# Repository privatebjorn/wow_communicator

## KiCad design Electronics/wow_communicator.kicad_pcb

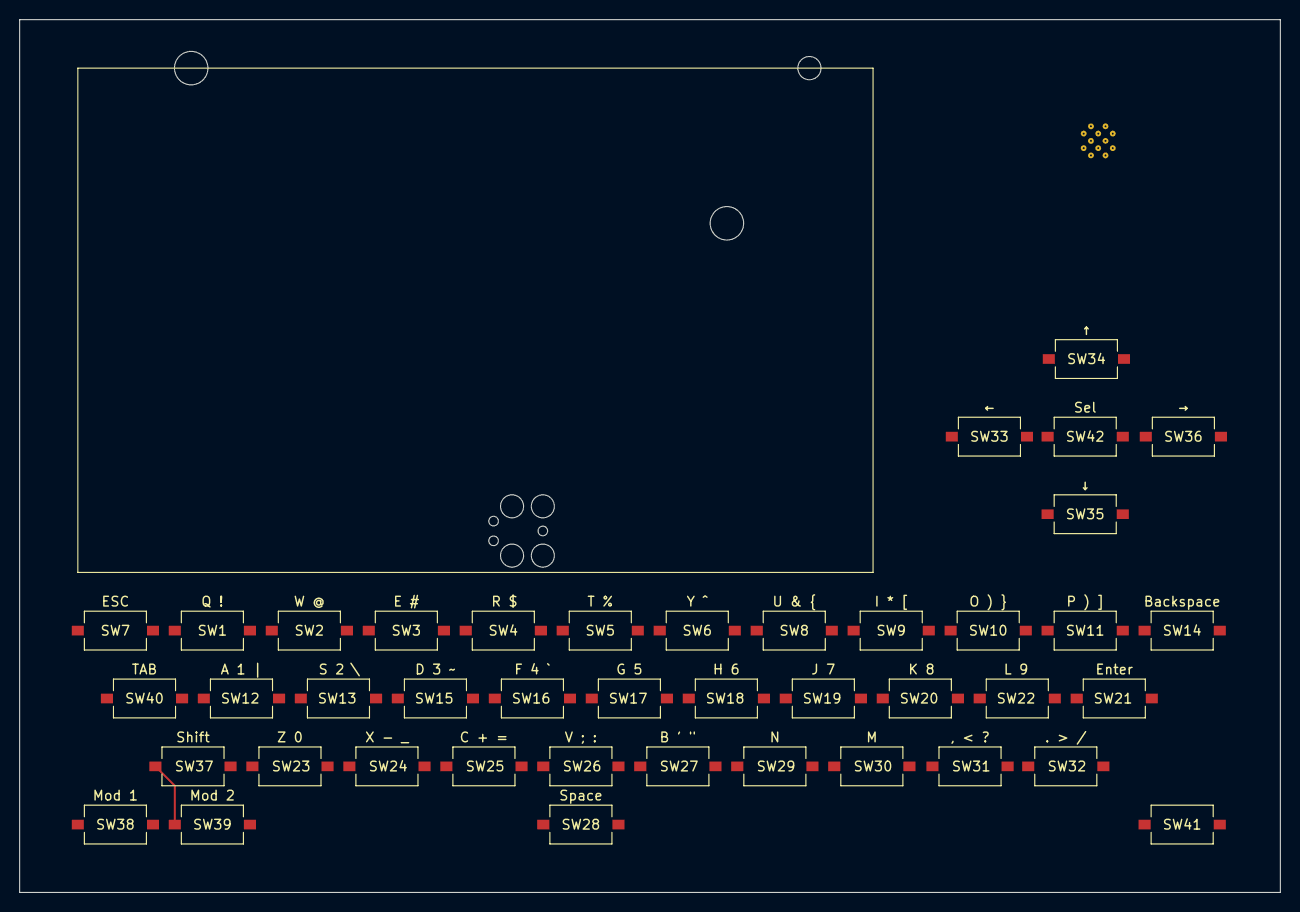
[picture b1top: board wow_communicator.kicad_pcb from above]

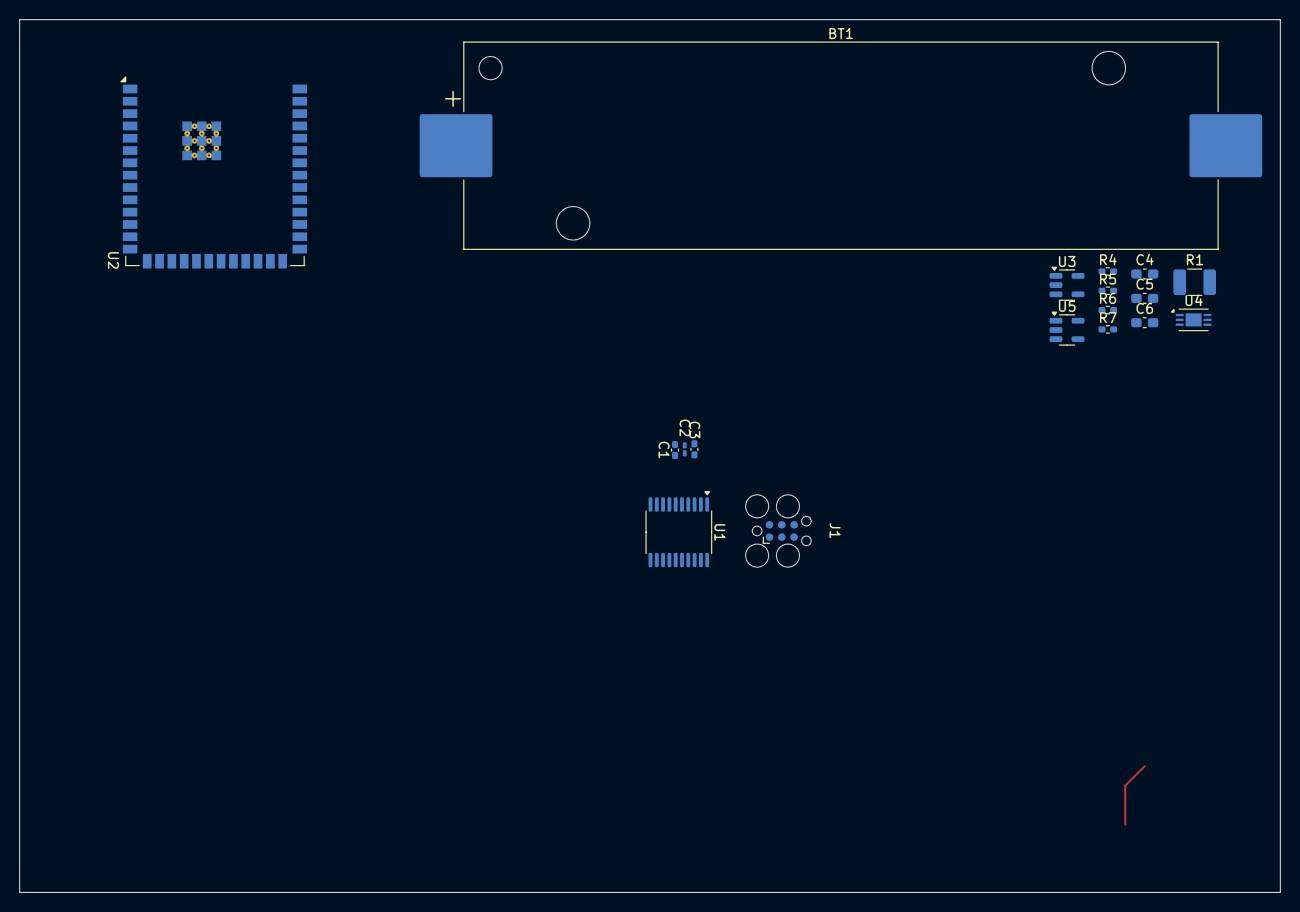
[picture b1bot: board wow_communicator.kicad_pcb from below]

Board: 4 copper layers, 130.0 x 90.0 mm, 60 parts (18 on the bottom side), 24 nets.

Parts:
BT1: 18650; BatteryHolder_Keystone_1042_1x18650
C1, C3: 100n; C_0402_1005Metric_Pad0.74x0.62mm_HandSolder
C2: 4.7u; C_0201_0603Metric_Pad0.64x0.40mm_HandSolder
C4: 1u; C_0603_1608Metric_Pad1.08x0.95mm_HandSolder
C5, C6: 10u; C_0603_1608Metric_Pad1.08x0.95mm_HandSolder
J1: DEBUG; Tag-Connect_TC2030-IDC-FP_2x03_P1.27mm_Vertical
R1: 100m; R_1210_3225Metric_Pad1.30x2.65mm_HandSolder
R4: 2k; R_0402_1005Metric_Pad0.72x0.64mm_HandSolder
R5, R6: 5.1k; R_0402_1005Metric_Pad0.72x0.64mm_HandSolder
R7: 1M; R_0402_1005Metric_Pad0.72x0.64mm_HandSolder
SW1, SW2, SW3, SW4, SW5, SW6, SW7, SW8, SW9, SW10, SW11, SW12, SW13, SW14, SW15, SW16, SW17, SW18, SW19, SW20, SW21, SW22, SW23, SW24, SW25, SW26, SW27, SW28, SW29, SW30, SW31, SW32, SW33, SW34, SW35, SW36, SW37, SW38, SW39, SW40, SW41, SW42: SW_SPST; SW_Tactile_SPST_NO_Straight_CK_PTS636Sx25SMTRLFS
U1: STM32C011F6Px; TSSOP-20_4.4x6.5mm_P0.65mm
U2: ESP32-S3-WROOM-2
U3: TLV75733PDBV; SOT-23-5
U4: LTC2942; DFN-6-1EP_3x2mm_P0.5mm_EP1.65x1.35mm
U5: MCP73812T-435I-OT; SOT-23-5

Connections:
0: BT1.2 (-), C1.2, C2.2, C3.2, C4.2, C5.2, C6.2, J1.5 (GND), R4.2, R5.2, R6.2, R7.2, U1.5 (VSS), U3.2 (GND), U4.2 (GND), U5.2 (V_{SS})
+3V3: C2.1, C3.1, C5.1, C6.1, J1.1 (VCC), U1.4 (VDD), U3.5 (OUT)
/keyboard_matrix/DEBUG_SWCLK: J1.4 (SWCLK), U1.19 (DEBUG_SWCLK)
/keyboard_matrix/DEBUG_SWDIO: J1.2 (SWDIO), U1.18 (DEBUG_SWDIO)
/keyboard_matrix/NRESET: C1.1, J1.3 (~RESET), U1.6 (PF2)
unnamed: BT1.1 (+), R1.2, U4.6 (SENSE-)
unnamed: SW1.1 (A), SW2.1 (A), SW3.1 (A), SW4.1 (A), SW5.1 (A), SW6.1 (A), SW7.1 (A), U1.15 (PA8)
unnamed: SW1.2 (B), SW8.2 (B), SW15.2 (B), SW22.2 (B), SW29.2 (B), SW36.2 (B), U1.14 (PA7)
unnamed: SW8.1 (A), SW9.1 (A), SW10.1 (A), SW11.1 (A), SW12.1 (A), SW13.1 (A), SW14.1 (A), U1.20 (PB6)
unnamed: SW3.2 (B), SW10.2 (B), SW17.2 (B), SW24.2 (B), SW31.2 (B), SW38.2 (B), U1.12 (PA5)
unnamed: SW4.2 (B), SW11.2 (B), SW18.2 (B), SW25.2 (B), SW32.2 (B), SW39.2 (B), U1.11 (PA4)
unnamed: SW5.2 (B), SW12.2 (B), SW19.2 (B), SW26.2 (B), SW33.2 (B), SW40.2 (B), U1.1 (PB7)
unnamed: SW6.2 (B), SW13.2 (B), SW20.2 (B), SW27.2 (B), SW34.2 (B), SW41.2 (B), U1.2 (PC14)
unnamed: SW7.2 (B), SW14.2 (B), SW21.2 (B), SW28.2 (B), SW35.2 (B), SW42.2 (B), U1.3 (PC15)
unnamed: SW15.1 (A), SW16.1 (A), SW17.1 (A), SW18.1 (A), SW19.1 (A), SW20.1 (A), SW21.1 (A), U1.10 (PA3)
unnamed: SW2.2 (B), SW9.2 (B), SW16.2 (B), SW23.2 (B), SW30.2 (B), SW37.2 (B), U1.13 (PA6)
unnamed: SW22.1 (A), SW23.1 (A), SW24.1 (A), SW25.1 (A), SW26.1 (A), SW27.1 (A), SW28.1 (A), U1.9 (PA2)
unnamed: SW29.1 (A), SW30.1 (A), SW31.1 (A), SW32.1 (A), SW33.1 (A), SW34.1 (A), SW35.1 (A), U1.8 (PA1)
unnamed: SW36.1 (A), SW37.1 (A), SW38.1 (A), SW39.1 (A), SW40.1 (A), SW41.1 (A), SW42.1 (A), U1.7 (PA0)
unnamed: C4.1, R1.1, U4.1 (SENSE+), U5.3 (V_{BAT})
unnamed: U3.1 (IN), U3.3 (EN)
unnamed: U2.1 (GND), U2.40 (GND), U2.41 (GND)
unnamed: U5.1 (CE), U5.4 (V_{DD})
unnamed: R4.1, U5.5 (PROG)

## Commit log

2025-07-20 added design notes
2025-07-20 completed keyboard schematic. added design note for stm32c0
2025-07-20 arranged keys for keyboard. marked out lcd
2025-07-20 basic power supply layout some minor design notes. charge ic likely to change. possibly bridge out fuel gague
2025-07-26 created LCD library started pinout
